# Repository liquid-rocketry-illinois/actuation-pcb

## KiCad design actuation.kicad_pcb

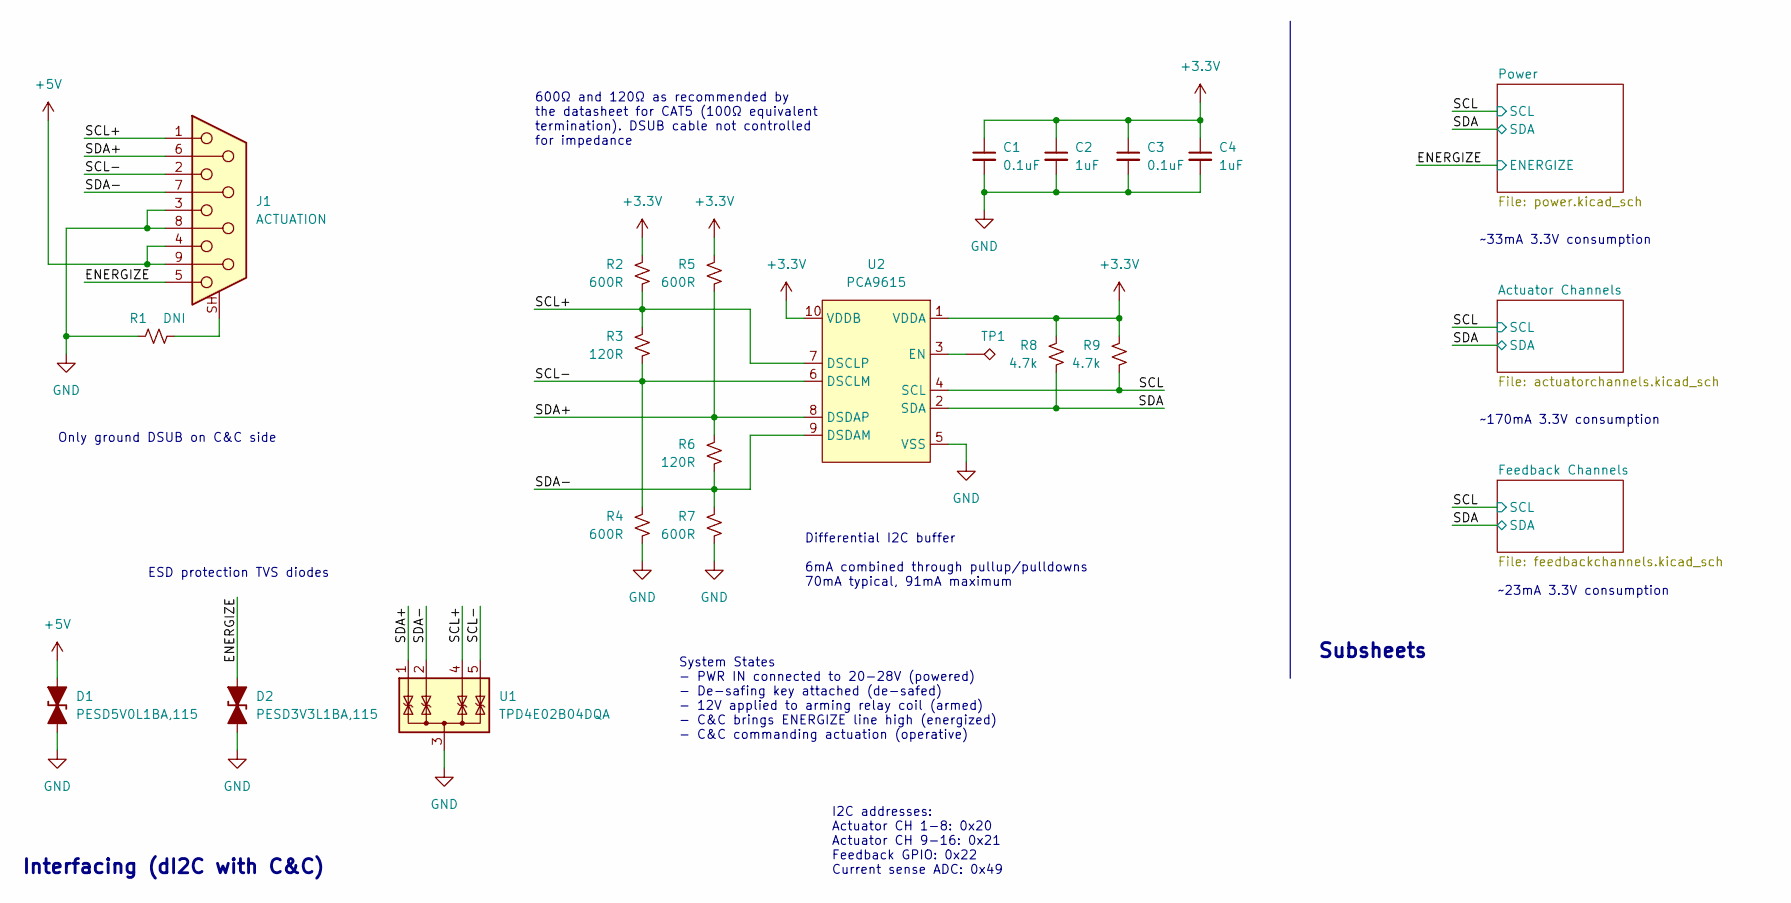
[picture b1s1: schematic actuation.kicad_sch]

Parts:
C1, C3: 0.1uF; C_0603_1608Metric
C2, C4: 1uF; C_0603_1608Metric
D1: PESD5V0L1BA,115; D_SOD-323; MPN PESD3V3L1BA,115
D2: PESD3V3L1BA,115; D_SOD-323; MPN PESD3V3L1BA,115
J1: ACTUATION; 182-009-213R561; MPN 182-009-213R561
R1: DNI; R_0603_1608Metric; MPN RC0603JR-070RL
R2, R4, R5, R7: 600R; R_0603_1608Metric
R3, R6: 120R; R_0603_1608Metric
R8, R9: 4.7k; R_0603_1608Metric
TP1: TestPoint_Alt; TestPoint_Pad_D2.0mm
U1: TPD4E02B04DQA; USON-10_2.5x1.0mm_P0.5mm; MPN TPD4E02B04DQAR
U2: PCA9615; TSSOP-10_3x3mm_P0.5mm; MPN PCA9615DPZ

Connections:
+3.3V: C1.1, C2.1, C3.1, C4.1, R2.1, R5.1, R8.1, R9.1, U2.1 (VDDA), U2.10 (VDDB); also elsewhere on the board
+5V: D1.2 (A2), J1.4, J1.9; also elsewhere on the board
/ENERGIZE: D2.2 (A2), J1.5; also elsewhere on the board
/SCL: R9.2, U2.4 (SCL); also elsewhere on the board
/SCL+: J1.1, R2.2, R3.1, U1.4 (IO3), U2.7 (DSCLP)
/SCL-: J1.2, R3.2, R4.1, U1.5 (IO4), U2.6 (DSCLM)
/SDA: R8.2, U2.2 (SDA); also elsewhere on the board
/SDA+: J1.6, R5.2, R6.1, U1.1 (IO1), U2.8 (DSDAP)
/SDA-: J1.7, R6.2, R7.1, U1.2 (IO2), U2.9 (DSDAM)
GND: C1.2, C2.2, C3.2, C4.2, D1.1 (A1), D2.1 (A1), J1.3, J1.8, R1.1, R4.2, R7.2, U1.3 (G), U1.8 (G), U2.5 (VSS); also elsewhere on the board
unnamed: J1.SH (PAD), R1.2
unnamed: TP1.1, U2.3 (EN)

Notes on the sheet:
~170mA 3.3V consumption
Interfacing (dI2C with C&C)
Subsheets
600Ω and 120Ω as recommended by the datasheet for CAT5 (100Ω equivalent termination). DSUB cable not controlled for impedance
~23mA 3.3V consumption
Only ground DSUB on C&C side
I2C addresses: Actuator CH 1-8: 0x20 Actuator CH 9-16: 0x21 Feedback GPIO: 0x22 Current sense ADC: 0x49
ESD protection TVS diodes
~33mA 3.3V consumption
System States - PWR IN connected to 20-28V (powered) - De-safing key attached (de-safed) - 12V applied to arming relay coil (armed) - C&C brings ENERGIZE line high (energized) - C&C commanding actuation (operative)
Differential I2C buffer 6mA combined through pullup/pulldowns 70mA typical, 91mA maximum

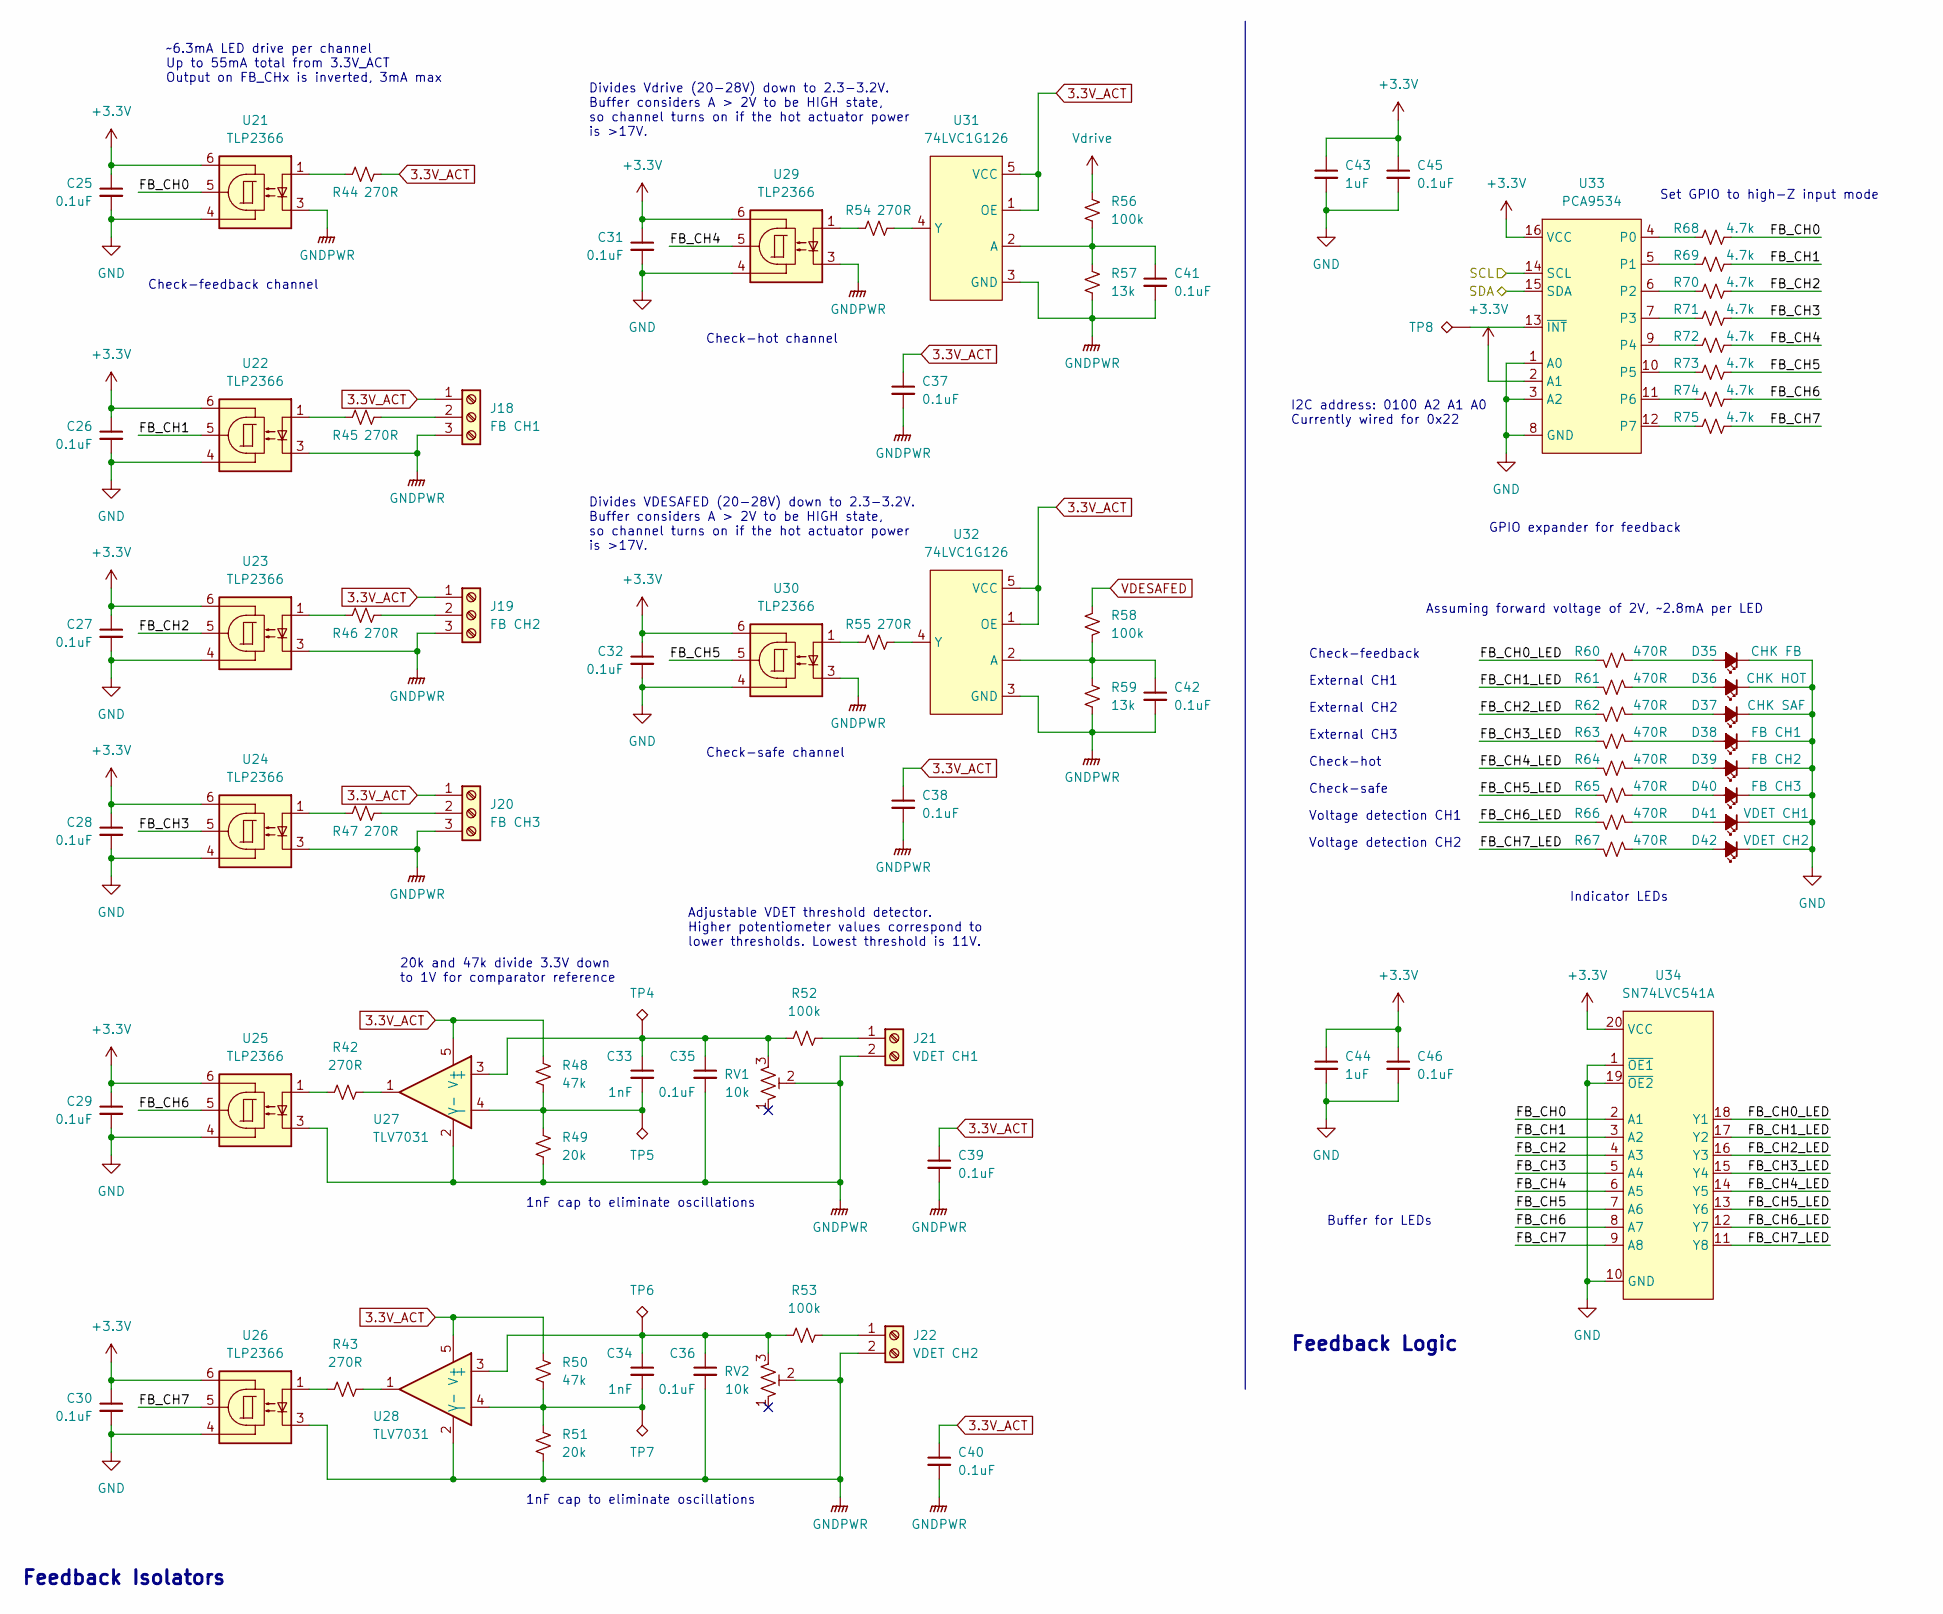
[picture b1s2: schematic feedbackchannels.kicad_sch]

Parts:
C25, C26, C27, C28, C29, C30, C31, C32, C35, C36, C37, C38, C39, C40, C41, C42, C45, C46: 0.1uF; C_0603_1608Metric
C33, C34: 1nF; C_0603_1608Metric
C43, C44: 1uF; C_0603_1608Metric
D35: CHK FB; LED_0603_1608Metric; MPN LTST-C191KGKT
D36: CHK HOT; LED_0603_1608Metric; MPN LTST-C191KRKT
D37: CHK SAF; LED_0603_1608Metric; MPN LTST-C191TBKT
D38: FB CH1; LED_0603_1608Metric; MPN LTST-C191TBKT
D39: FB CH2; LED_0603_1608Metric; MPN LTST-C191TBKT
D40: FB CH3; LED_0603_1608Metric; MPN LTST-C191TBKT
D41: VDET CH1; LED_0603_1608Metric; MPN LTST-C191TBKT
D42: VDET CH2; LED_0603_1608Metric; MPN LTST-C191TBKT
J18: FB CH1; 1935174; MPN 1935174
J19: FB CH2; 1935174; MPN 1935174
J20: FB CH3; 1935174; MPN 1935174
J21: VDET CH1; 1935161; MPN 1935161
J22: VDET CH2; 1935161; MPN 1935161
R42, R43, R44, R45, R46, R47, R54, R55: 270R; R_0603_1608Metric; MPN RC0603FR-07270RL
R48, R50: 47k; R_0603_1608Metric
R49, R51: 20k; R_0603_1608Metric
R52, R53, R56, R58: 100k; R_0603_1608Metric
R57, R59: 13k; R_0603_1608Metric
R60, R61, R62, R63, R64, R65, R66, R67: 470R; R_0603_1608Metric
R68, R69, R70, R71, R72, R73, R74, R75: 4.7k; R_0603_1608Metric
RV1, RV2: 10k; Potentiometer_Bourns_3224W_Vertical; MPN 3224W-1-103E
TP4, TP5, TP6, TP7, TP8: TestPoint_Alt; TestPoint_Pad_D2.0mm
U21, U22, U23, U24, U25, U26, U29, U30: TLP2366; MPN TLP2366(V4-TPL,E
U27, U28: TLV7031; SOT-353_SC-70-5; MPN TLV7031QDCKRQ1
U31, U32: 74LVC1G126; SOT-23-5; MPN 74LVC1G126GV,125
U33: PCA9534; TSSOP-16_4.4x5mm_P0.65mm; MPN PCA9534PWR
U34: SN74LVC541A; TSSOP-20_4.4x6.5mm_P0.65mm; MPN SN74LVC541APWR

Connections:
3.3V_ACT: C37.1, C38.1, C39.1, C40.1, J18.1, J19.1, J20.1, R44.2, R48.1, R50.1, U27.5 (V+), U28.5 (V+), U31.1 (OE), U31.5 (VCC), U32.1 (OE), U32.5 (VCC); also elsewhere on the board
+3.3V: C25.1, C26.1, C27.1, C28.1, C29.1, C30.1, C31.1, C32.1, C43.1, C44.1, C45.1, C46.1, U21.6, U22.6, U23.6, U24.6, U25.6, U26.6, U29.6, U30.6, U33.2 (A1), U33.16 (VCC), U34.20 (VCC); also elsewhere on the board
/Feedback Channels/FB_CH0: R68.2, U21.5, U34.2 (A1)
/Feedback Channels/FB_CH0_LED: R60.1, U34.18 (Y1)
/Feedback Channels/FB_CH1: R69.2, U22.5, U34.3 (A2)
/Feedback Channels/FB_CH1_LED: R61.1, U34.17 (Y2)
/Feedback Channels/FB_CH2: R70.2, U23.5, U34.4 (A3)
/Feedback Channels/FB_CH2_LED: R62.1, U34.16 (Y3)
/Feedback Channels/FB_CH3: R71.2, U24.5, U34.5 (A4)
/Feedback Channels/FB_CH3_LED: R63.1, U34.15 (Y4)
/Feedback Channels/FB_CH4: R72.2, U29.5, U34.6 (A5)
/Feedback Channels/FB_CH4_LED: R64.1, U34.14 (Y5)
/Feedback Channels/FB_CH5: R73.2, U30.5, U34.7 (A6)
/Feedback Channels/FB_CH5_LED: R65.1, U34.13 (Y6)
/Feedback Channels/FB_CH6: R74.2, U25.5, U34.8 (A7)
/Feedback Channels/FB_CH6_LED: R66.1, U34.12 (Y7)
/Feedback Channels/FB_CH7: R75.2, U26.5, U34.9 (A8)
/Feedback Channels/FB_CH7_LED: R67.1, U34.11 (Y8)
/SCL: U33.14 (SCL); also elsewhere on the board
/SDA: U33.15 (SDA); also elsewhere on the board
GND: C25.2, C26.2, C27.2, C28.2, C29.2, C30.2, C31.2, C32.2, C43.2, C44.2, C45.2, C46.2, D35.1 (K), D36.1 (K), D37.1 (K), D38.1 (K), D39.1 (K), D40.1 (K), D41.1 (K), D42.1 (K), U21.4, U22.4, U23.4, U24.4, U25.4, U26.4, U29.4, U30.4, U33.1 (A0), U33.3 (A2), U33.8 (GND), U34.1 (~OE1), U34.10 (GND), U34.19 (~OE2); also elsewhere on the board
GNDPWR: C35.2, C36.2, C37.2, C38.2, C39.2, C40.2, C41.2, C42.2, J18.3, J19.3, J20.3, J21.2, J22.2, R49.2, R51.2, R57.2, R59.2, RV1.2, RV2.2, U21.3, U22.3, U23.3, U24.3, U25.3, U26.3, U27.2 (V-), U28.2 (V-), U29.3, U30.3, U31.3 (GND), U32.3 (GND); also elsewhere on the board
unnamed: C33.1, C35.1, R52.1, RV1.3, TP4.1, U27.3 (+)
unnamed: C33.2, R48.2, R49.1, TP5.1, U27.4 (-)
unnamed: C34.1, C36.1, R53.1, RV2.3, TP6.1, U28.3 (+)
unnamed: C34.2, R50.2, R51.1, TP7.1, U28.4 (-)
unnamed: C41.1, R56.2, R57.1, U31.2 (A)
unnamed: C42.1, R58.2, R59.1, U32.2 (A)
unnamed: D35.2 (A), R60.2
unnamed: D36.2 (A), R61.2
unnamed: D37.2 (A), R62.2
unnamed: D38.2 (A), R63.2
unnamed: D39.2 (A), R64.2
unnamed: D40.2 (A), R65.2
unnamed: D41.2 (A), R66.2
unnamed: D42.2 (A), R67.2
unnamed: J18.2, R45.2
unnamed: J19.2, R46.2
unnamed: J20.2, R47.2
unnamed: J21.1, R52.2
unnamed: J22.1, R53.2
unnamed: R42.1, U25.1
unnamed: R42.2, U27.1
unnamed: R43.1, U26.1
unnamed: R43.2, U28.1
unnamed: R44.1, U21.1
unnamed: R45.1, U22.1
unnamed: R46.1, U23.1
unnamed: R47.1, U24.1
unnamed: R54.1, U31.4 (Y)
unnamed: R54.2, U29.1
unnamed: R55.1, U32.4 (Y)
unnamed: R55.2, U30.1
unnamed: R68.1, U33.4 (P0)
unnamed: R69.1, U33.5 (P1)
unnamed: R70.1, U33.6 (P2)
unnamed: R71.1, U33.7 (P3)
unnamed: R72.1, U33.9 (P4)
unnamed: R73.1, U33.10 (P5)
unnamed: R74.1, U33.11 (P6)
unnamed: R75.1, U33.12 (P7)
unnamed: TP8.1, U33.13 (~INT)
VDESAFED: R58.1; also elsewhere on the board
Vdrive: R56.1; also elsewhere on the board

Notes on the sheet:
Check-feedback channel
Indicator LEDs
Buffer for LEDs
1nF cap to eliminate oscillations
Voltage detection CH1
I2C address: 0100 A2 A1 A0 Currently wired for 0x22
Check-hot
Set GPIO to high-Z input mode
Voltage detection CH2
Check-hot channel
Assuming forward voltage of 2V, ~2.8mA per LED
20k and 47k divide 3.3V down to 1V for comparator reference
Divides Vdrive (20-28V) down to 2.3-3.2V. Buffer considers A > 2V to be HIGH state, so channel turns on if the hot actuator power is >17V.
Check-safe channel
~6.3mA LED drive per channel Up to 55mA total from 3.3V_ACT Output on FB_CHx is inverted, 3mA max
Feedback Isolators
External CH2
External CH1
GPIO expander for feedback
Adjustable VDET threshold detector. Higher potentiometer values correspond to lower thresholds. Lowest threshold is 11V.
Check-feedback
External CH3
Divides VDESAFED (20-28V) down to 2.3-3.2V. Buffer considers A > 2V to be HIGH state, so channel turns on if the hot actuator power is >17V.
Check-safe
Feedback Logic

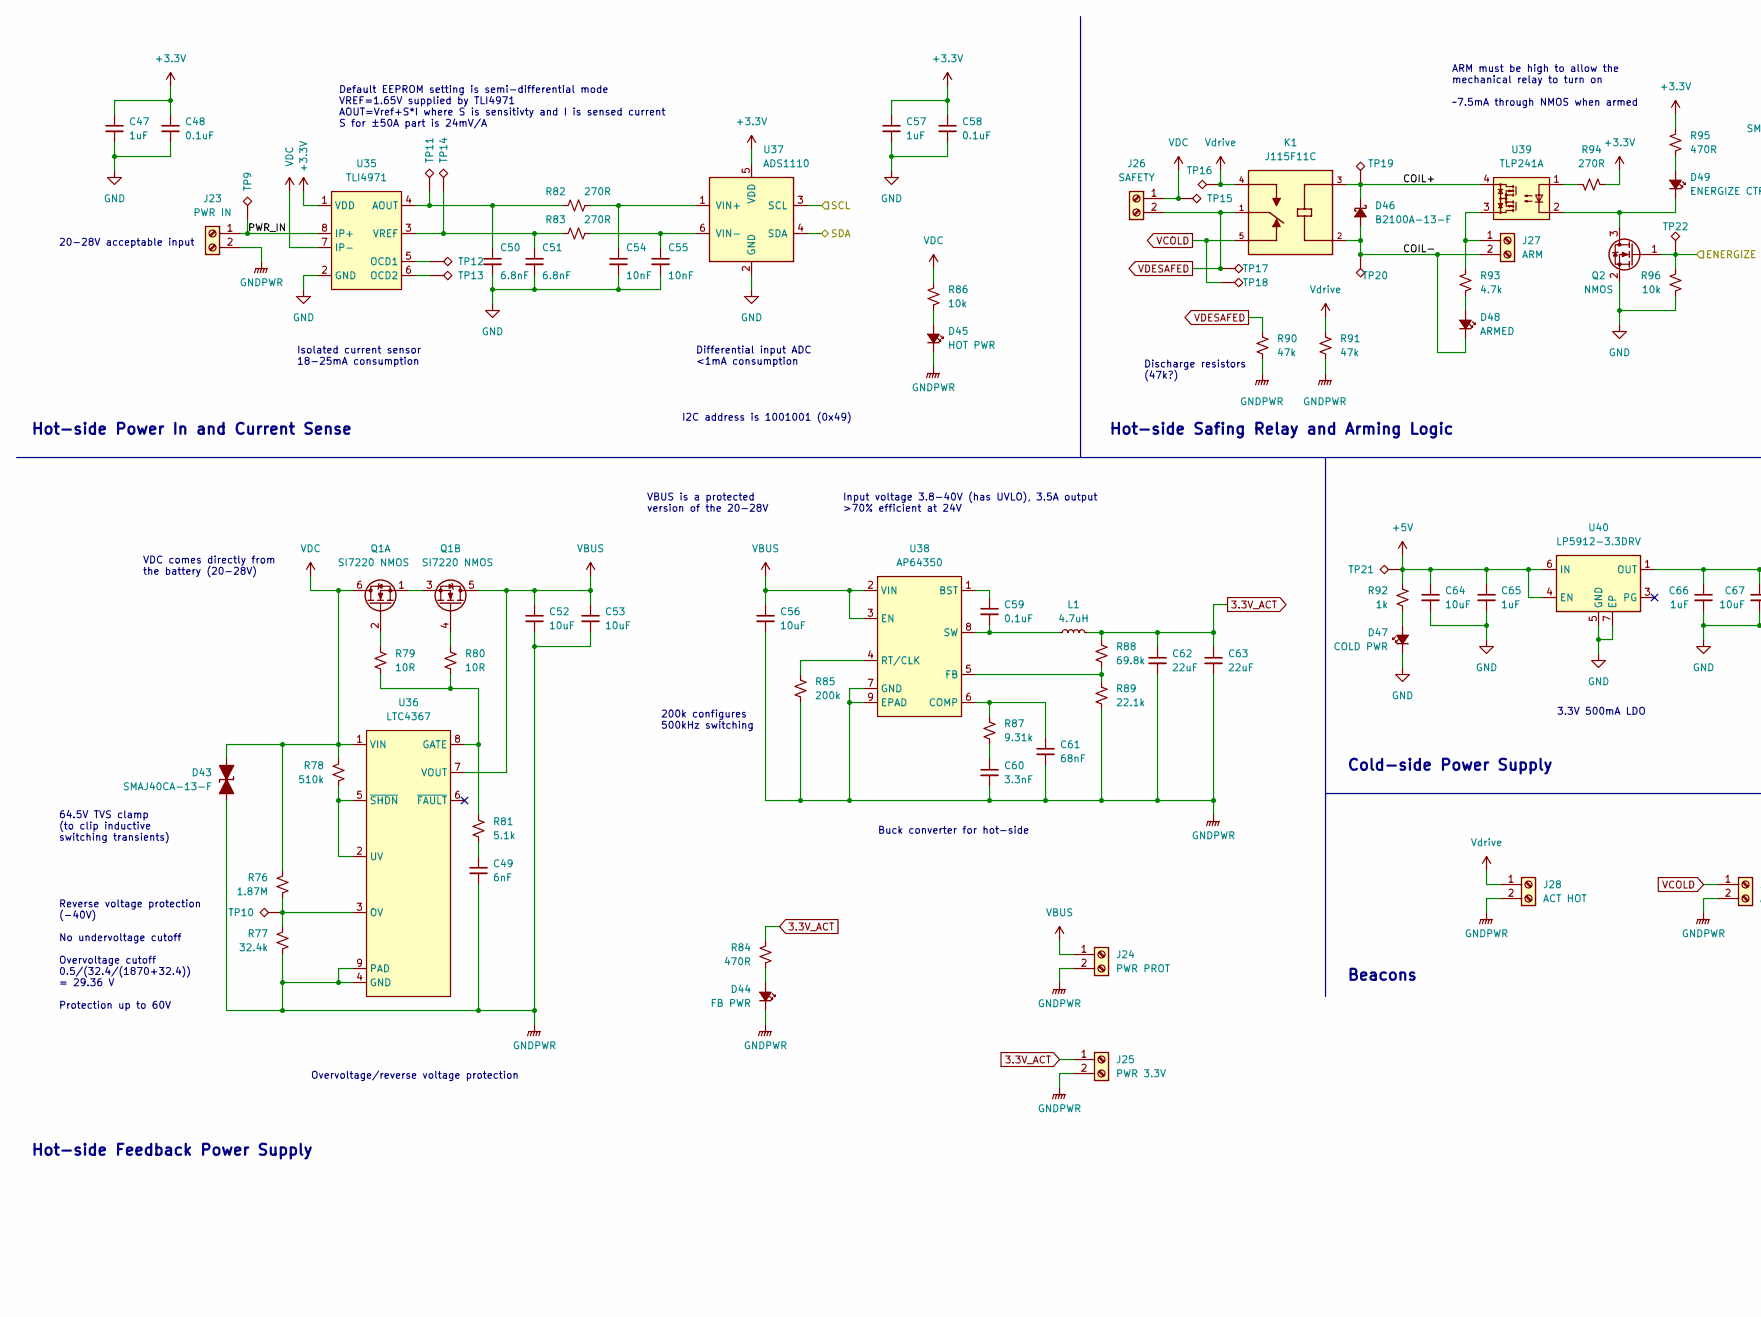
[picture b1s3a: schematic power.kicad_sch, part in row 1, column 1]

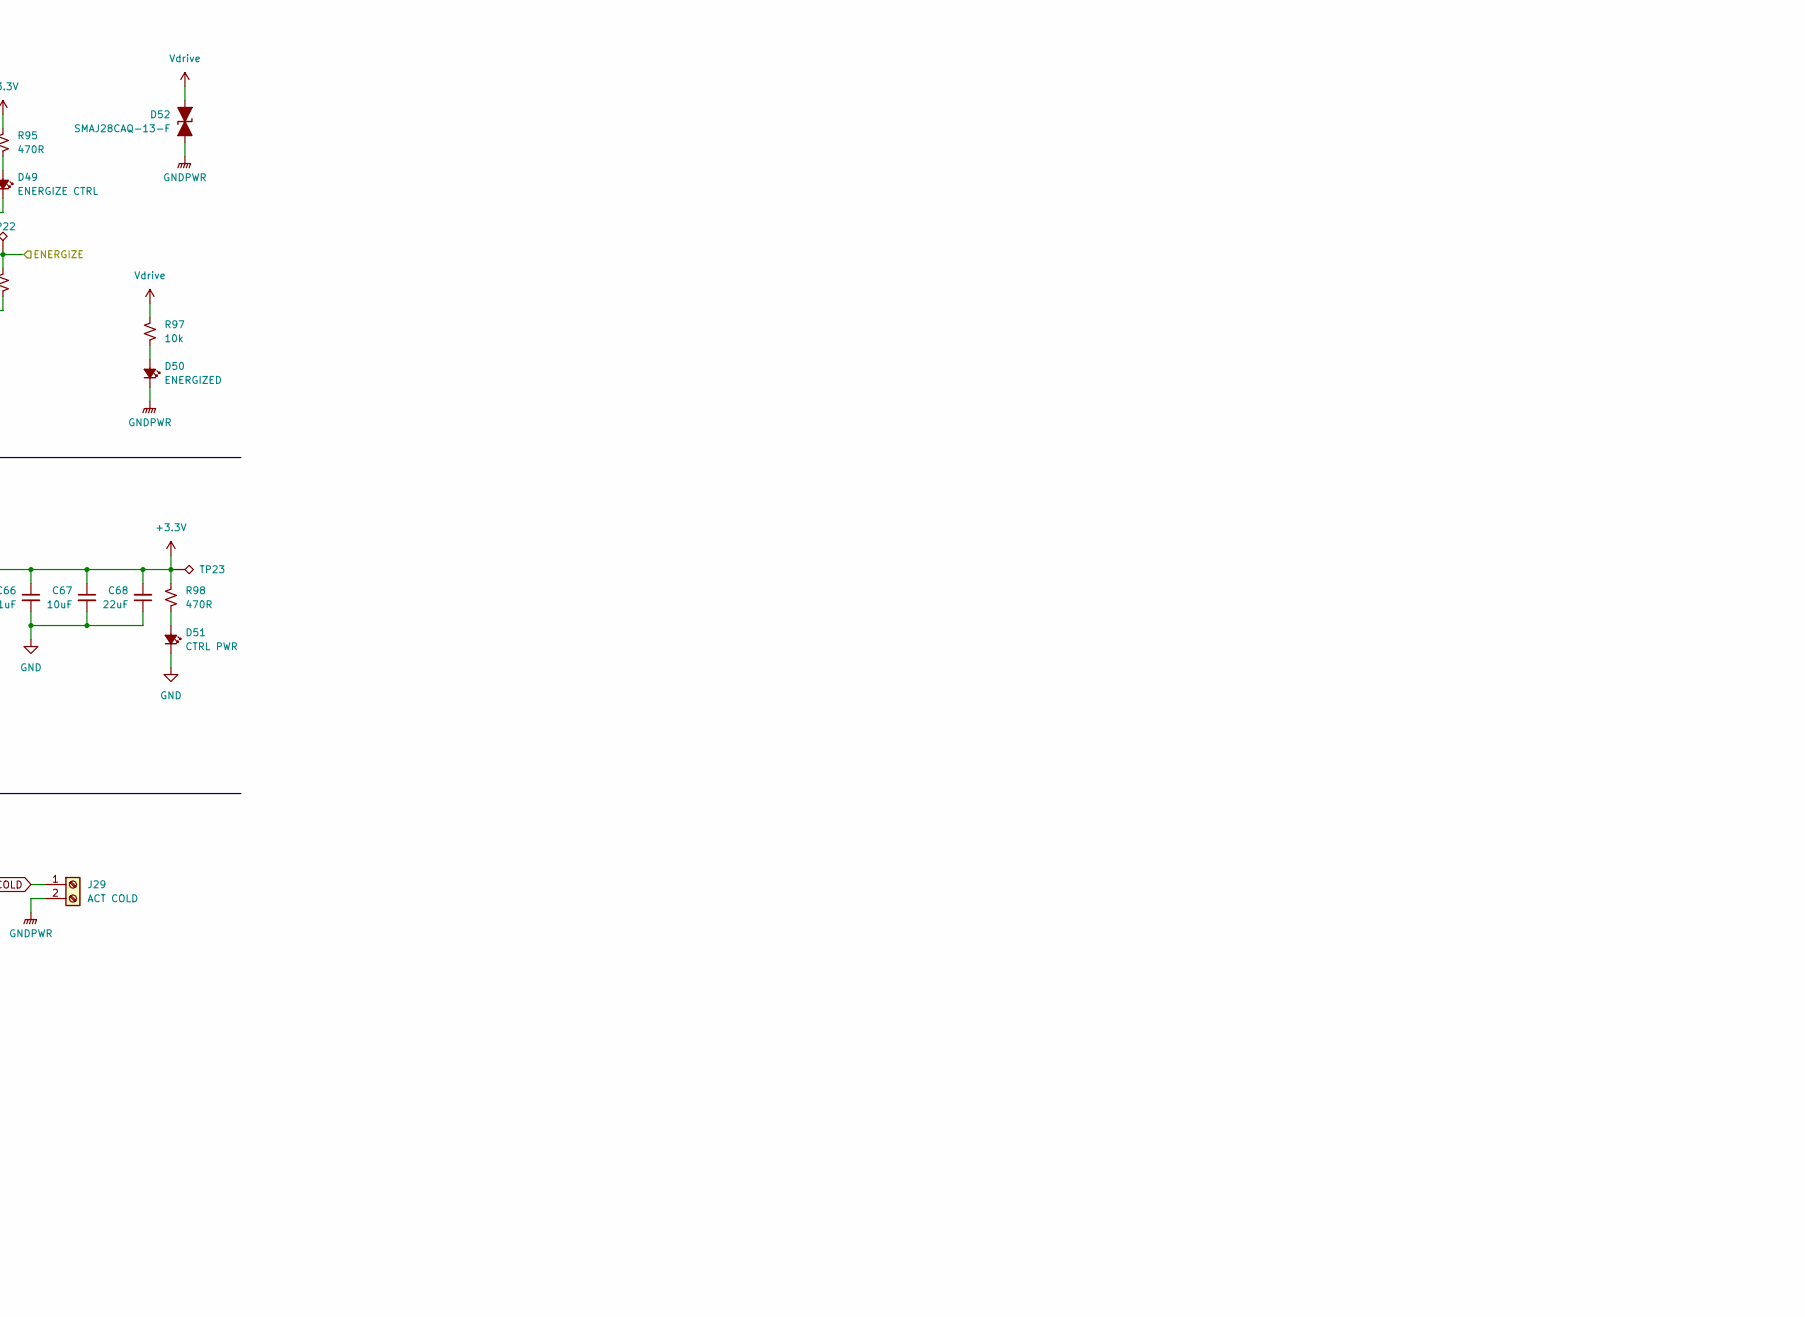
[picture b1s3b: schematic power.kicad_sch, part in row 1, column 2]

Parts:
C47, C57, C65, C66: 1uF; C_0603_1608Metric
C48, C58, C59: 0.1uF; C_0603_1608Metric
C49: 6nF; C_0603_1608Metric; MPN CL10C060DB8NNNC
C50, C51: 6.8nF; C_0603_1608Metric
C52, C53, C56: 10uF; C_1206_3216Metric; MPN CL31B106KBHNNNE
C54, C55: 10nF; C_0603_1608Metric
C60: 3.3nF; C_0603_1608Metric
C61: 68nF; C_0603_1608Metric
C62, C63, C68: 22uF; C_1206_3216Metric
C64, C67: 10uF; C_0805_2012Metric
D43: SMAJ40CA-13-F; D_SMA; MPN SMAJ40CA-13-F
D44: FB PWR; LED_0603_1608Metric; MPN LTST-C191KGKT
D45: HOT PWR; LED_0603_1608Metric; MPN LTST-C191KGKT
D46: B2100A-13-F; D_SMA; MPN B2100A-13-F
D47: COLD PWR; LED_0603_1608Metric; MPN LTST-C191KGKT
D48: ARMED; LED_0603_1608Metric; MPN LTST-C191KRKT
D49: ENERGIZE CTRL; LED_0603_1608Metric; MPN LTST-C191KRKT
D50: ENERGIZED; LED_0603_1608Metric; MPN LTW-C191DS5
D51: CTRL PWR; LED_0603_1608Metric; MPN LTST-C191KGKT
D52: SMAJ28CAQ-13-F; D_SMA; MPN SMAJ28CAQ-13-F
J23: PWR IN; XT90PW-M; MPN XT90PW-M
J24: PWR PROT; AMASS_XT60-M_1x02_P7.20mm_Vertical; MPN XT60-M
J25: PWR 3.3V; AMASS_XT60-M_1x02_P7.20mm_Vertical; MPN XT60-M
J26: SAFETY; XT90PW-M; MPN XT90PW-M
J27: ARM; AMASS_XT60-M_1x02_P7.20mm_Vertical; MPN XT60-M
J28: ACT HOT; AMASS_XT60-M_1x02_P7.20mm_Vertical; MPN XT60-M
J29: ACT COLD; AMASS_XT60-M_1x02_P7.20mm_Vertical; MPN XT60-M
K1: J115F11C; MPN J115F11CH12VDCSH1.5U
L1: 4.7uH; L_Vishay_IHLP-2020; MPN IHLP2020CZER4R7M11
Q1: SI7220 NMOS; Vishay_PowerPAK_1212-8_Dual; MPN SI7220DN-T1-GE3
Q2: NMOS; SOT-23-3; MPN PMV40UN2R
R76: 1.87M; R_0603_1608Metric; MPN RC0603FR-071M87L
R77: 32.4k; R_0603_1608Metric; MPN RT0603BRD0732K4L
R78: 510k; R_0603_1608Metric; MPN RC0603FR-07510KL
R79, R80: 10R; R_0603_1608Metric; MPN RC0603FR-0710RL
R81: 5.1k; R_0603_1608Metric
R82, R83, R94: 270R; R_0603_1608Metric; MPN RC0603FR-07270RL
R84, R95, R98: 470R; R_0603_1608Metric
R85: 200k; R_0603_1608Metric
R86, R96, R97: 10k; R_0603_1608Metric
R87: 9.31k; R_0603_1608Metric
R88: 69.8k; R_0603_1608Metric
R89: 22.1k; R_0603_1608Metric
R90, R91: 47k; R_0603_1608Metric
R92: 1k; R_0603_1608Metric
R93: 4.7k; R_0603_1608Metric
TP9, TP10, TP11, TP12, TP13, TP14, TP15, TP16, TP17, TP18, TP19, TP20, TP21, TP22, TP23: TestPoint_Alt; TestPoint_Pad_D2.0mm
U35: TLI4971; Infineon_PG-TISON-8-5; MPN TLI4971A050T5UE0001XUMA1
U36: LTC4367; DFN-8-1EP_3x3mm_P0.5mm_EP1.65x2.38mm; MPN LTC4367IDD-1#PBF
U37: ADS1110; SOT-23-6; MPN ADS1110A1IDBVT
U38: AP64350; SOIC-8-1EP_3.9x4.9mm_P1.27mm_EP2.62x3.51mm; MPN AP64350SP-13
U39: TLP241A; MPN TLP241A(TP1,F
U40: LP5912-3.3DRV; WSON-6-1EP_2x2mm_P0.65mm_EP1x1.6mm; MPN LP5912-3.3DRVR

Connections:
3.3V_ACT: C62.1, C63.1, J25.1, L1.2, R84.1, R88.1; also elsewhere on the board
+3.3V: C47.1, C48.1, C57.1, C58.1, C66.1, C67.1, C68.2, R94.1, R95.1, R98.1, TP23.1, U35.1 (VDD), U37.5 (VDD), U40.1 (OUT); also elsewhere on the board
+5V: C64.1, C65.1, R92.1, TP21.1, U40.4 (EN), U40.6 (IN); also elsewhere on the board
/ENERGIZE: Q2.1 (G), R96.1, TP22.1; also elsewhere on the board
/Power/COIL+: D46.1 (K), K1.3, TP19.1, U39.4
/Power/COIL-: D46.2 (A), D48.1 (K), J27.2, K1.2, TP20.1
/Power/PWR_IN: J23.1, TP9.1, U35.8 (IP+)
/SCL: U37.3 (SCL); also elsewhere on the board
/SDA: U37.4 (SDA); also elsewhere on the board
GND: C47.2, C48.2, C50.2, C51.2, C54.2, C55.2, C57.2, C58.2, C64.2, C65.2, C66.2, C67.2, C68.1, D47.1 (K), D51.1 (K), Q2.2 (S), R96.2, U35.2 (GND), U37.2 (GND), U40.5 (GND), U40.7 (EP); also elsewhere on the board
GNDPWR: C49.2, C52.2, C53.2, C56.2, C60.2, C61.2, C62.2, C63.2, D43.1 (A1), D44.1 (K), D45.1 (K), D50.1 (K), D52.1 (A1), J23.2, J24.2, J25.2, J28.2, J29.2, R77.1, R85.2, R89.2, R90.2, R91.2, U36.4 (GND), U36.9 (PAD), U38.7 (GND), U38.9 (EPAD); also elsewhere on the board
unnamed: C49.1, R81.2
unnamed: C50.1, R82.1, TP11.1, U35.4 (AOUT)
unnamed: C51.1, R83.1, TP14.1, U35.3 (VREF)
unnamed: C54.1, R82.2, U37.1 (VIN+)
unnamed: C55.1, R83.2, U37.6 (VIN-)
unnamed: C59.1, U38.1 (BST)
unnamed: C59.2, L1.1, U38.8 (SW)
unnamed: C60.1, R87.2
unnamed: C61.1, R87.1, U38.6 (COMP)
unnamed: D44.2 (A), R84.2
unnamed: D45.2 (A), R86.2
unnamed: D47.2 (A), R92.2
unnamed: D48.2 (A), R93.2
unnamed: D49.1 (K), Q2.3 (D), U39.2
unnamed: D49.2 (A), R95.2
unnamed: D50.2 (A), R97.2
unnamed: D51.2 (A), R98.2
unnamed: J27.1, R93.1, U39.3
unnamed: Q1.1 (S), Q1.3 (S)
unnamed: Q1.2 (G), R79.1
unnamed: Q1.4 (G), R80.1
unnamed: R76.1, R77.2, TP10.1, U36.3 (OV)
unnamed: R78.1, U36.2 (UV), U36.5 (~SHDN)
unnamed: R79.2, R80.2, R81.1, U36.8 (GATE)
unnamed: R85.1, U38.4 (RT/CLK)
unnamed: R88.2, R89.1, U38.5 (FB)
unnamed: R94.2, U39.1
unnamed: TP12.1, U35.5 (OCD1)
unnamed: TP13.1, U35.6 (OCD2)
VBUS: C52.1, C53.1, C56.1, J24.1, Q1.5 (D), U36.7 (VOUT), U38.2 (VIN), U38.3 (EN)
VCOLD: J29.1, K1.5, TP18.1
VDC: D43.2 (A2), J26.1, Q1.6 (D), R76.2, R78.2, R86.1, TP15.1, U35.7 (IP-), U36.1 (VIN)
VDESAFED: J26.2, K1.1, R90.1, TP17.1; also elsewhere on the board
Vdrive: D52.2 (A2), J28.1, K1.4, R91.1, R97.1, TP16.1; also elsewhere on the board

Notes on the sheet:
Hot-side Feedback Power Supply
64.5V TVS clamp (to clip inductive switching transients)
Input voltage 3.8-40V (has UVLO), 3.5A output >70% efficient at 24V
VBUS is a protected version of the 20-28V
Isolated current sensor 18-25mA consumption
Cold-side Power Supply
Differential input ADC <1mA consumption
3.3V 500mA LDO
Buck converter for hot-side
Overvoltage/reverse voltage protection
VDC comes directly from the battery (20-28V)
200k configures 500kHz switching
Hot-side Power In and Current Sense
I2C address is 1001001 (0x49)
Beacons
Reverse voltage protection (-40V) No undervoltage cutoff Overvoltage cutoff 0.5/(32.4/(1870+32.4)) = 29.36 V Protection up to 60V
20-28V acceptable input
Hot-side Safing Relay and Arming Logic
ARM must be high to allow the mechanical relay to turn on ~7.5mA through NMOS when armed
Default EEPROM setting is semi-differential mode VREF=1.65V supplied by TLI4971 AOUT=Vref+S*I where S is sensitivty and I is sensed current S for ±50A part is 24mV/A
Discharge resistors (47k?)
